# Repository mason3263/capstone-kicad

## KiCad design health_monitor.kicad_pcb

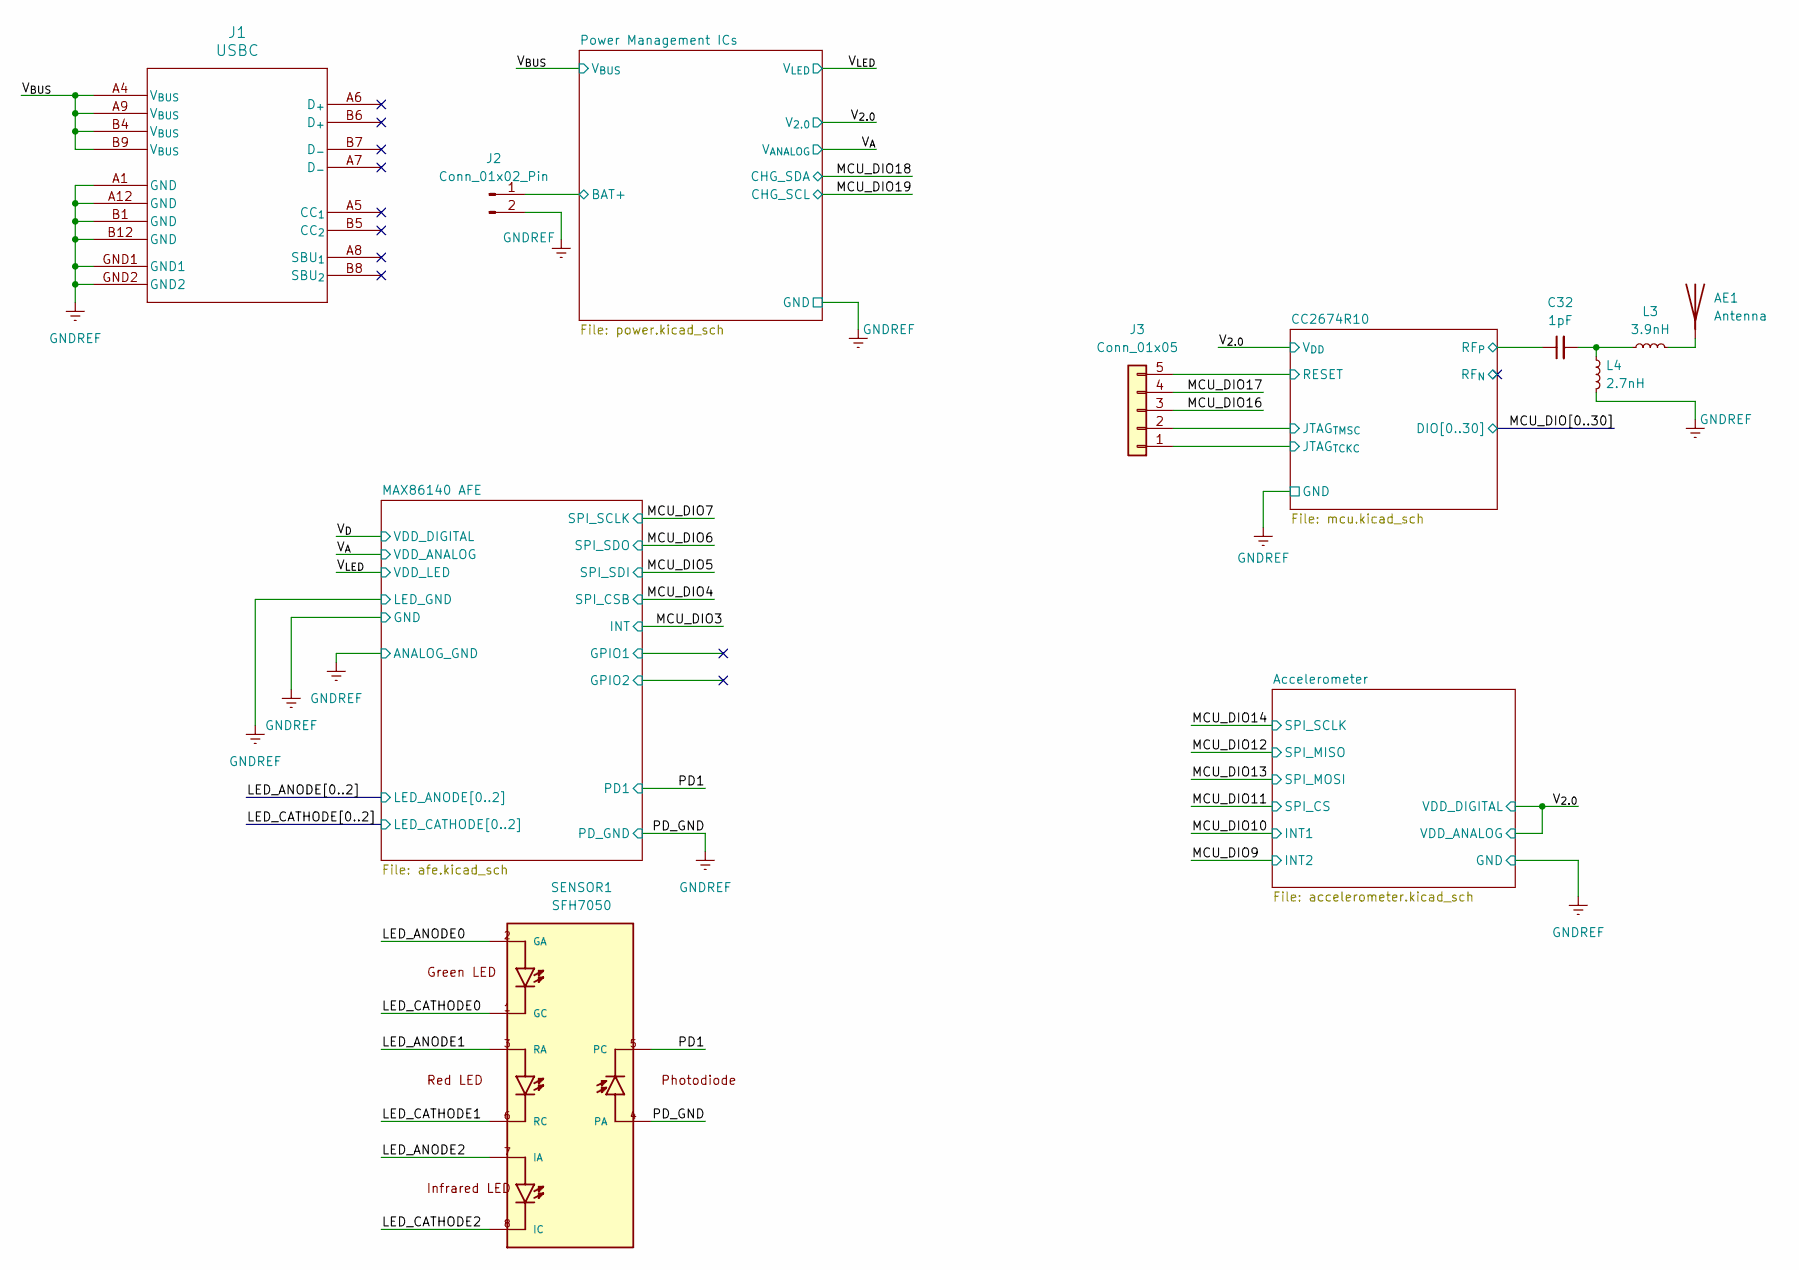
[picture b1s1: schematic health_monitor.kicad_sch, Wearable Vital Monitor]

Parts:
AE1: Antenna; Johanson_2450AT18x100; LCSC PN C89334
C32: 1pF; C_0603_1608Metric
J1: USBC; MOLEX_USBC_1054500101; LCSC PN C134092
J2: Conn_01x02_Pin; PinHeader_1x02_P2.54mm_Vertical
J3: Conn_01x05; PinHeader_1x05_P2.54mm_Vertical
L3: 3.9nH; L_0603_1608Metric
L4: 2.7nH; L_0603_1608Metric
SENSOR1: SFH7050; SFH 7050A_OSM

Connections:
/CC2674R10/JTAG_{TCKC}: J3.1; also elsewhere on the board
/CC2674R10/JTAG_{TMSC}: J3.2; also elsewhere on the board
/CC2674R10/RESET: J3.5; also elsewhere on the board
/CC2674R10/RF_{P}: C32.1; also elsewhere on the board
/LED_CATHODE0: SENSOR1.1 (GC); also elsewhere on the board
/LED_CATHODE1: SENSOR1.6 (RC); also elsewhere on the board
/LED_CATHODE2: SENSOR1.8 (IC); also elsewhere on the board
/MCU_DIO16: J3.3; also elsewhere on the board
/MCU_DIO17: J3.4; also elsewhere on the board
/PD1: SENSOR1.5 (PC); also elsewhere on the board
/Power Management ICs/BAT+: J2.1; also elsewhere on the board
/V_{BUS}: J1.A4 (V_{BUS}), J1.A9 (V_{BUS}), J1.B4 (V_{BUS}), J1.B9 (V_{BUS}); also elsewhere on the board
/V_{LED}: SENSOR1.2 (GA), SENSOR1.3 (RA), SENSOR1.7 (IA); also elsewhere on the board
GNDREF: J1.A1 (GND), J1.A12 (GND), J1.B1 (GND), J1.B12 (GND), J1.GND1, J1.GND2, J2.2, L4.2, SENSOR1.4 (PA); also elsewhere on the board
unnamed: AE1.1 (A), L3.2
unnamed: C32.2, L3.1, L4.1

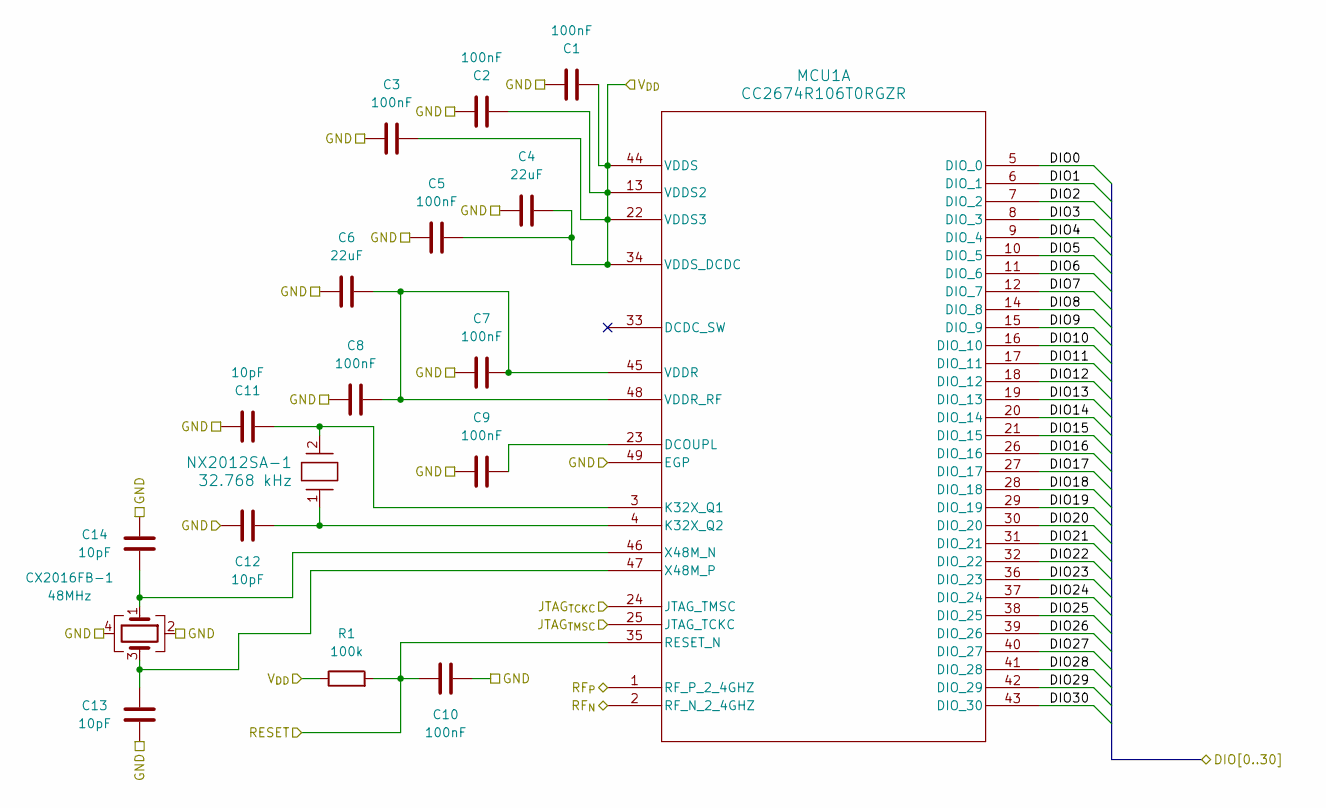
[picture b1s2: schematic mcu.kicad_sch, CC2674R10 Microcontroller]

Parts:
C1, C2, C3, C5, C7, C8, C9: 100nF; C_0603_1608Metric
C4, C6: 22uF; C_0603_1608Metric
C10: 100nF; C_0603_1608Metric_Pad1.08x0.95mm_HandSolder
C11, C12, C13, C14: 10pF; C_0603_1608Metric
CX2016FB-1: 48MHz; Crystal_SMD_2016-4Pin_2.0x1.6mm; LCSC PN C5186571
MCU1: CC2674R106T0RGZR; CC2647R106T0RGZR
NX2012SA-1: 32.768 kHz; Crystal_SMD_2012-2Pin_2.0x1.2mm; LCSC PN C891748
R1: 100k; R_0603_1608Metric

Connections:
/CC2674R10/JTAG_{TCKC}: MCU1.24 (JTAG_TMSC); also elsewhere on the board
/CC2674R10/JTAG_{TMSC}: MCU1.25 (JTAG_TCKC); also elsewhere on the board
/CC2674R10/RESET: C10.1, MCU1.35 (RESET_N), R1.2; also elsewhere on the board
/CC2674R10/RF_{N}: MCU1.2 (RF_N_2_4GHZ)
/CC2674R10/RF_{P}: MCU1.1 (RF_P_2_4GHZ); also elsewhere on the board
/MCU_DIO0: MCU1.5 (DIO_0)
/MCU_DIO1: MCU1.6 (DIO_1)
/MCU_DIO2: MCU1.7 (DIO_2)
/MCU_DIO3: MCU1.8 (DIO_3); also elsewhere on the board
/MCU_DIO4: MCU1.9 (DIO_4); also elsewhere on the board
/MCU_DIO5: MCU1.10 (DIO_5); also elsewhere on the board
/MCU_DIO6: MCU1.11 (DIO_6); also elsewhere on the board
/MCU_DIO7: MCU1.12 (DIO_7); also elsewhere on the board
/MCU_DIO8: MCU1.14 (DIO_8)
/MCU_DIO9: MCU1.15 (DIO_9); also elsewhere on the board
/MCU_DIO10: MCU1.16 (DIO_10); also elsewhere on the board
/MCU_DIO11: MCU1.17 (DIO_11); also elsewhere on the board
/MCU_DIO12: MCU1.18 (DIO_12); also elsewhere on the board
/MCU_DIO13: MCU1.19 (DIO_13); also elsewhere on the board
/MCU_DIO14: MCU1.20 (DIO_14); also elsewhere on the board
/MCU_DIO15: MCU1.21 (DIO_15)
/MCU_DIO16: MCU1.26 (DIO_16); also elsewhere on the board
/MCU_DIO17: MCU1.27 (DIO_17); also elsewhere on the board
/MCU_DIO18: MCU1.28 (DIO_18); also elsewhere on the board
/MCU_DIO19: MCU1.29 (DIO_19); also elsewhere on the board
/MCU_DIO20: MCU1.30 (DIO_20)
/MCU_DIO21: MCU1.31 (DIO_21)
/MCU_DIO22: MCU1.32 (DIO_22)
/MCU_DIO23: MCU1.36 (DIO_23)
/MCU_DIO24: MCU1.37 (DIO_24)
/MCU_DIO25: MCU1.38 (DIO_25)
/MCU_DIO26: MCU1.39 (DIO_26)
/MCU_DIO27: MCU1.40 (DIO_27)
/MCU_DIO28: MCU1.41 (DIO_28)
/MCU_DIO29: MCU1.42 (DIO_29)
/MCU_DIO30: MCU1.43 (DIO_30)
/V_{2.0}: C1.1, C2.1, C3.1, C4.2, C5.1, MCU1.13 (VDDS2), MCU1.22 (VDDS3), MCU1.34 (VDDS_DCDC), MCU1.44 (VDDS), R1.1; also elsewhere on the board
GNDREF: C1.2, C2.2, C3.2, C4.1, C5.2, C6.1, C7.2, C8.2, C9.2, C10.2, C11.2, C12.1, C13.2, C14.1, CX2016FB-1.2, CX2016FB-1.4, MCU1.49 (EGP); also elsewhere on the board
unnamed: C9.1, MCU1.23 (DCOUPL)
unnamed: C11.1, MCU1.3 (K32X_Q1), NX2012SA-1.2
unnamed: C12.2, MCU1.4 (K32X_Q2), NX2012SA-1.1
unnamed: C6.2, C7.1, C8.1, MCU1.45 (VDDR), MCU1.48 (VDDR_RF)
unnamed: C14.2, CX2016FB-1.1, MCU1.46 (X48M_N)
unnamed: C13.1, CX2016FB-1.3, MCU1.47 (X48M_P)

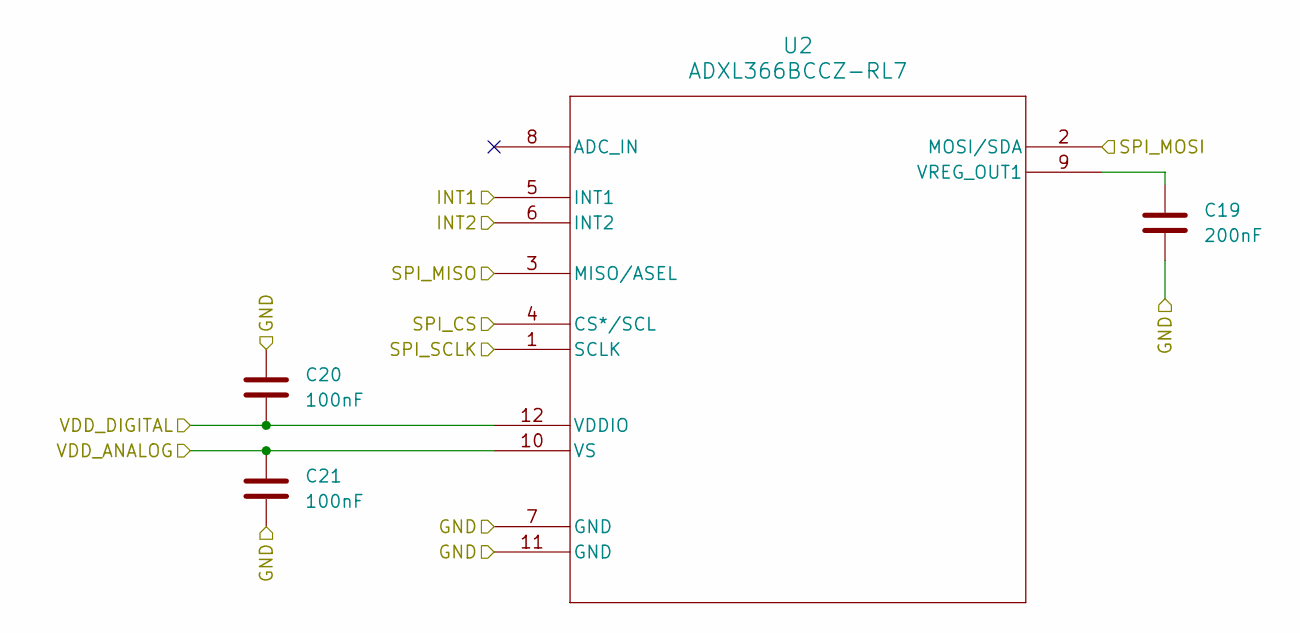
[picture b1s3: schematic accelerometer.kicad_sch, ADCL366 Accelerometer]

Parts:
C19: 200nF; C_0603_1608Metric
C20, C21: 100nF; C_0603_1608Metric
U2: ADXL366BCCZ-RL7

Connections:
/MCU_DIO9: U2.6 (INT2); also elsewhere on the board
/MCU_DIO10: U2.5 (INT1); also elsewhere on the board
/MCU_DIO11: U2.4 (CS*/SCL); also elsewhere on the board
/MCU_DIO12: U2.3 (MISO/ASEL); also elsewhere on the board
/MCU_DIO13: U2.2 (MOSI/SDA); also elsewhere on the board
/MCU_DIO14: U2.1 (SCLK); also elsewhere on the board
/V_{2.0}: C20.2, C21.1, U2.10 (VS), U2.12 (VDDIO); also elsewhere on the board
GNDREF: C19.2, C20.1, C21.2, U2.7 (GND), U2.11 (GND); also elsewhere on the board
unnamed: C19.1, U2.9 (VREG_OUT1)

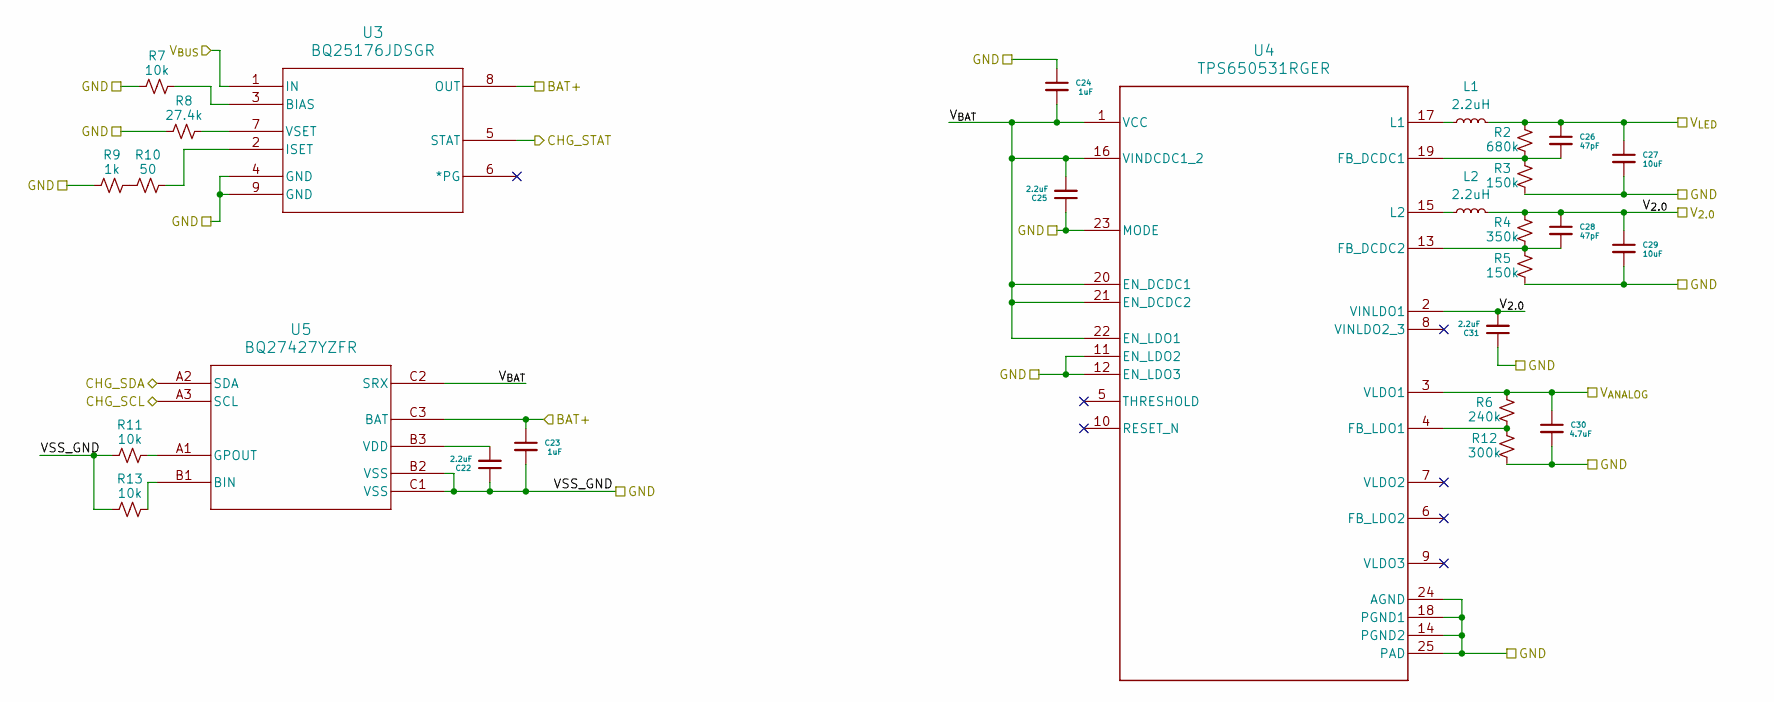
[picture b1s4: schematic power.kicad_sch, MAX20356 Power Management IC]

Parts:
C22, C25, C31: 2.2uF; C_0603_1608Metric
C23, C24: 1uF; C_0603_1608Metric
C26, C28: 47pF; C_0603_1608Metric
C27, C29: 10uF; C_0603_1608Metric
C30: 4.7uF; C_0603_1608Metric
L1, L2: 2.2uH; L_1008_2520Metric; LCSC PN C23894
R2: 680k; R_0603_1608Metric
R3, R5: 150k; R_0603_1608Metric
R4: 350k; R_0603_1608Metric
R6: 240k; R_0603_1608Metric
R7, R11, R13: 10k; R_0603_1608Metric
R8: 27.4k; R_0603_1608Metric
R9: 1k; R_0603_1608Metric
R10: 50; R_0603_1608Metric
R12: 300k; R_0603_1608Metric
U3: BQ25176JDSGR; BQ25176; LCSC PN C22407142
U4: TPS650531RGER; TPS650531; LCSC PN C527526
U5: BQ27427YZFR; BQ27427

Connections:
/MCU_DIO18: U5.A2 (SDA); also elsewhere on the board
/MCU_DIO19: U5.A3 (SCL); also elsewhere on the board
/Power Management ICs/BAT+: C23.1, U3.8 (OUT), U5.C3 (BAT); also elsewhere on the board
/Power Management ICs/CHG_STAT: U3.5 (STAT)
/Power Management ICs/V_{BAT}: C24.2, C25.2, U4.1 (VCC), U4.16 (VINDCDC1_2), U4.20 (EN_DCDC1), U4.21 (EN_DCDC2), U4.22 (EN_LDO1), U5.C2 (SRX)
/V_{2.0}: C28.1, C29.1, C31.2, L2.2, R4.2, U4.2 (VINLDO1); also elsewhere on the board
/V_{A}: C30.1, R6.2, U4.3 (VLDO1); also elsewhere on the board
/V_{BUS}: U3.1 (IN); also elsewhere on the board
/V_{LED}: C26.1, C27.1, L1.2, R2.2; also elsewhere on the board
GNDREF: C22.1, C23.2, C24.1, C25.1, C27.2, C29.2, C30.2, C31.1, R3.1, R5.1, R7.1, R8.1, R9.1, R11.1, R12.1, R13.1, U3.4 (GND), U3.9 (GND), U4.11 (EN_LDO2), U4.12 (EN_LDO3), U4.14 (PGND2), U4.18 (PGND1), U4.23 (MODE), U4.24 (AGND), U4.25 (PAD), U4.V1, U4.V2, U4.V3, U4.V4, U4.V5, U5.B2 (VSS), U5.C1 (VSS); also elsewhere on the board
unnamed: R9.2, R10.1
unnamed: R7.2, U3.3 (BIAS)
unnamed: R10.2, U3.2 (ISET)
unnamed: R8.2, U3.7 (VSET)
unnamed: C26.2, R2.1, R3.2, U4.19 (FB_DCDC1)
unnamed: C28.2, R4.1, R5.2, U4.13 (FB_DCDC2)
unnamed: R6.1, R12.2, U4.4 (FB_LDO1)
unnamed: L1.1, U4.17 (L1)
unnamed: L2.1, U4.15 (L2)
unnamed: R13.2, U5.B1 (BIN)
unnamed: R11.2, U5.A1 (GPOUT)
unnamed: C22.2, U5.B3 (VDD)

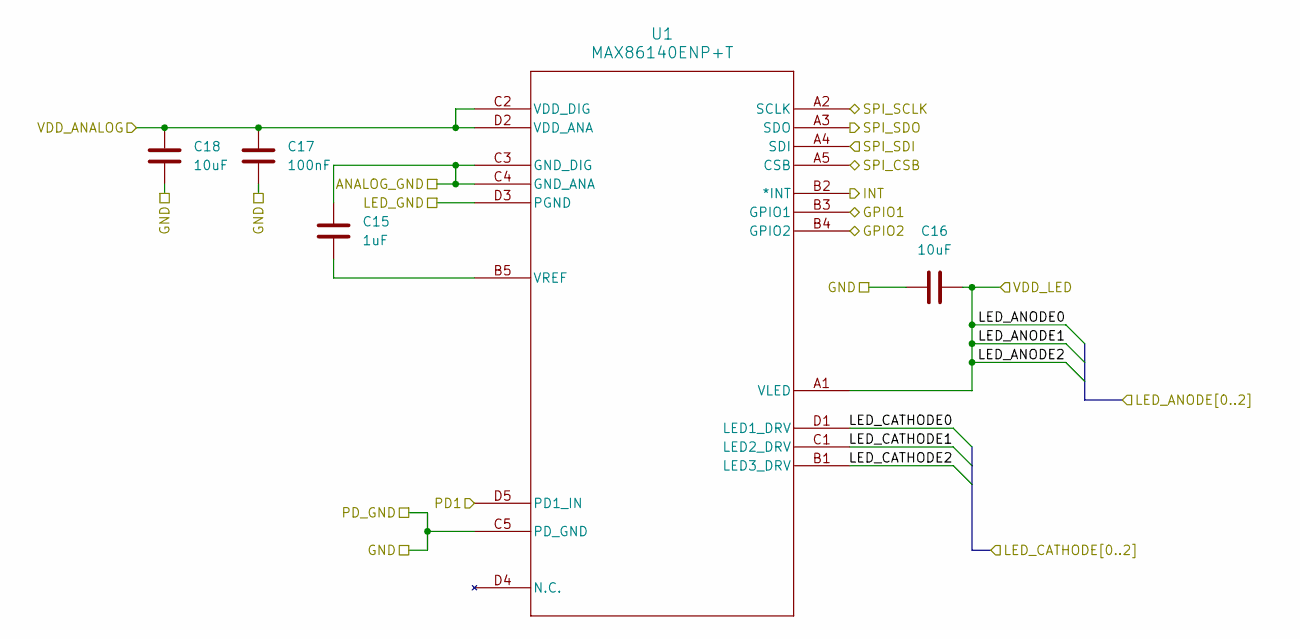
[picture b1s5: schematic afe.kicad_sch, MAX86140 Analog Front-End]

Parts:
C15: 1uF; C_0603_1608Metric
C16, C18: 10uF; C_0603_1608Metric
C17: 100nF; C_0603_1608Metric
U1: MAX86140ENP+T

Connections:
/LED_CATHODE0: U1.D1 (LED1_DRV); also elsewhere on the board
/LED_CATHODE1: U1.C1 (LED2_DRV); also elsewhere on the board
/LED_CATHODE2: U1.B1 (LED3_DRV); also elsewhere on the board
/MAX86140 AFE/GPIO1: U1.B3 (GPIO1)
/MAX86140 AFE/GPIO2: U1.B4 (GPIO2)
/MCU_DIO3: U1.B2 (*INT); also elsewhere on the board
/MCU_DIO4: U1.A5 (CSB); also elsewhere on the board
/MCU_DIO5: U1.A4 (SDI); also elsewhere on the board
/MCU_DIO6: U1.A3 (SDO); also elsewhere on the board
/MCU_DIO7: U1.A2 (SCLK); also elsewhere on the board
/PD1: U1.D5 (PD1_IN); also elsewhere on the board
/V_{A}: C17.1, C18.1, U1.C2 (VDD_DIG), U1.D2 (VDD_ANA); also elsewhere on the board
/V_{LED}: C16.2, U1.A1 (VLED); also elsewhere on the board
GNDREF: C15.1, C16.1, C17.2, C18.2, U1.C3 (GND_DIG), U1.C4 (GND_ANA), U1.C5 (PD_GND), U1.D3 (PGND); also elsewhere on the board
unnamed: C15.2, U1.B5 (VREF)

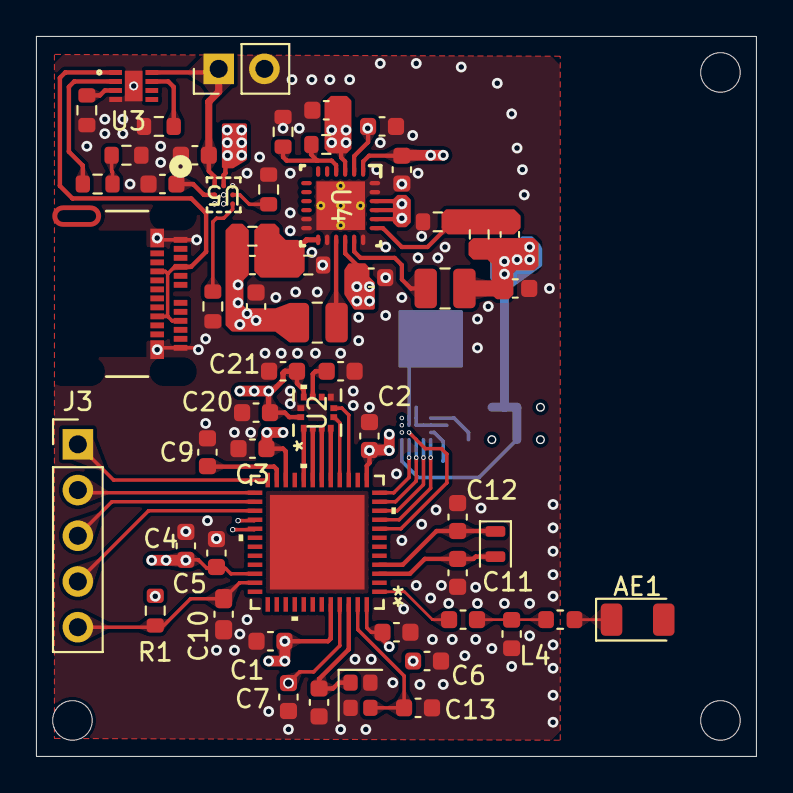
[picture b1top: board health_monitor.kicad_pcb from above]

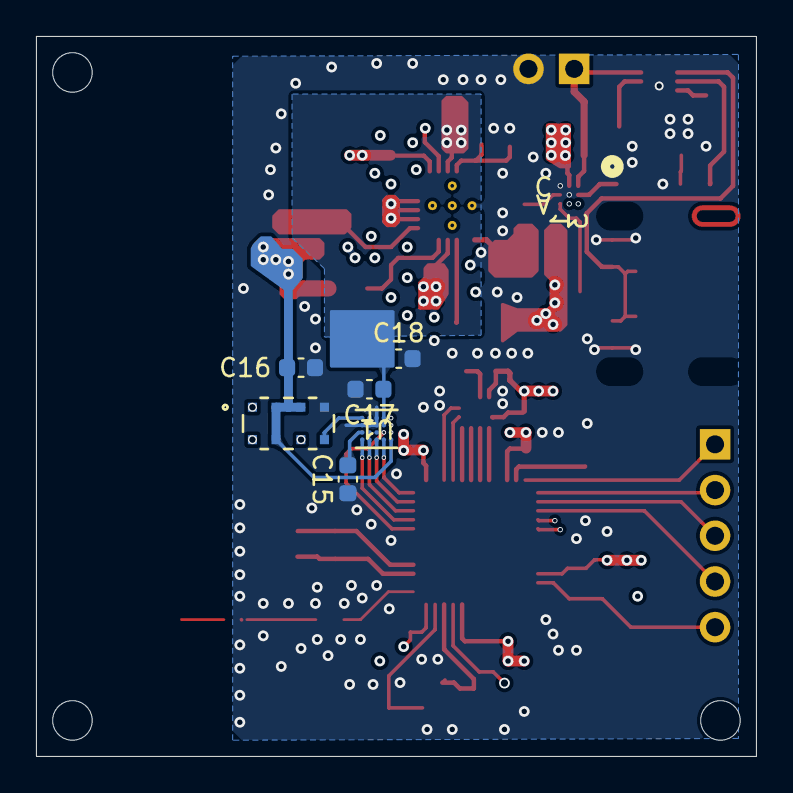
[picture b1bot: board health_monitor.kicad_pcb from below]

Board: 4 copper layers, 40.0 x 40.0 mm, 65 parts (6 on the bottom side), 52 nets.

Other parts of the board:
P1, P2: (no value)
P3: MountingHole_2.2mm_M2

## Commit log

2025-11-12 init
2025-11-21 MCU Submodule done
2025-11-25 schematic 90%
2025-12-02 General Structure
2026-01-15 inital routing
2026-01-30 schematic mostly finished
2026-02-17 ready to order
2026-02-19 resize to 0603
2026-02-19 final order
2026-02-23 final
2026-02-24 fix 4am horrors
